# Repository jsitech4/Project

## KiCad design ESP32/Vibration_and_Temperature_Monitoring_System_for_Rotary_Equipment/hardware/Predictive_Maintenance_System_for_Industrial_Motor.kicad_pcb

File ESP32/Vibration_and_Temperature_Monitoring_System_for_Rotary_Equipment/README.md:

# Predictive Maintenance System for Industrial Motor

## Overview

This project is a complete **Predictive Maintenance System for Industrial Motor Monitoring** built around the **ESP32-S3 WROOM-1U** using a modular **PlatformIO** firmware structure.

The system is designed to monitor an industrial motor in real time, detect abnormal behaviour, estimate future fault risk, store large amounts of data for later analysis, and provide a local web dashboard for live viewing.

The system monitors:

- Motor vibration using an **ADXL345 accelerometer**
- Motor current using a **ZMCT103C current sensor**
- Motor temperature using a **DS18B20 temperature sensor**
- Motor operating state using a relay protection system

The system then calculates:

- Motor health score
- Motor risk score
- Fault level
- Worst operating metric
- Future fault estimate
- Maintenance recommendation

The project is designed so that the **SD card acts as the main backend and storage device**. If the SD card is not available, the firmware automatically uses the ESP32-S3 internal flash memory through **LittleFS** as fallback storage.

---

# Main Goal

The goal of this project is not only to display sensor values, but to behave like a real predictive maintenance prototype.

It should be able to:

1. Monitor motor operating condition
2. Log sensor and analysis data
3. Detect abnormal current, temperature, and vibration
4. Predict possible fault trends
5. Protect the motor using a relay
6. Notify the user using buzzer and LED indication
7. Display live status on LCD
8. Provide a web dashboard for future analysis
9. Store enough data for later engineering analysis

---

# Features

- ESP32-S3 WROOM-1U based controller
- ADXL345 vibration monitoring
- ZMCT103C current monitoring
- DS18B20 temperature monitoring
- 20x4 I2C LCD display
- Rotary encoder navigation
- Relay-based motor protection
- Active buzzer alarm
- Breathing onboard LED indicator
- SD card backend storage
- Internal LittleFS fallback storage
- CSV data logging
- Event logging
- Predictive maintenance analysis
- Motor health score calculation
- Risk score calculation
- Future fault estimation
- Local Wi-Fi Access Point
- Web dashboard for live monitoring
- Downloadable CSV logs from web dashboard
- Modular PlatformIO project structure
- Non-blocking firmware design

---

# Hardware Used

## Main Controller

- ESP32-S3 WROOM-1U

## Display

- 20x4 I2C LCD screen

## Sensors

- ADXL345 vibration sensor
- ZMCT103C current sensor
- DS18B20 temperature sensor

## Storage

- MicroSD card module
- ESP32-S3 internal flash memory using LittleFS as fallback

## User Input

- Rotary encoder with push button

## Output / Protection

- Relay module
- Active buzzer
- Onboard status LED

## Programming Interface

- CH340C USB-to-serial converter

---

# Pin Configuration

## I2C Bus

The LCD and ADXL345 share the same I2C bus.

| Function | ESP32-S3 GPIO |
|---|---|
| I2C SDA | GPIO8 |
| I2C SCL | GPIO9 |
| LCD SDA | GPIO8 |
| LCD SCL | GPIO9 |
| ADXL345 SDA | GPIO8 |
| ADXL345 SCL | GPIO9 |

---

## ADXL345 Vibration Sensor

| Function | ESP32-S3 GPIO |
|---|---|
| SDA | GPIO8 |
| SCL | GPIO9 |
| INT | GPIO10 |

---

## ZMCT103C Current Sensor

| Function | ESP32-S3 GPIO |
|---|---|
| Analog Output | GPIO1 |

> The ZMCT103C output must be conditioned properly and must not exceed the ESP32-S3 ADC input range.

---

## DS18B20 Temperature Sensor

| Function | ESP32-S3 GPIO |
|---|---|
| DATA | GPIO4 |

> Use a 4.7k pull-up resistor between DATA and 3.3V.

---

## SD Card Module

The SD card uses SPI mode.

| Function | ESP32-S3 GPIO |
|---|---|
| CS | GPIO5 |
| MOSI | GPIO11 |
| SCK | GPIO12 |
| MISO | GPIO13 |

---

## Rotary Encoder

| Function | ESP32-S3 GPIO |
|---|---|
| CLK | GPIO16 |
| DT | GPIO17 |
| SW | GPIO18 |

---

## Output Devices

| Function | ESP32-S3 GPIO |
|---|---|
| Buzzer | GPIO14 |
| Relay | GPIO21 |
| Status LED | GPIO48 |

---

## CH340C USB-to-Serial

| CH340C Pin | ESP32-S3 GPIO |
|---|---|
| TXD | GPIO44 RX0 |
| RXD | GPIO43 TX0 |
| GND | GND |

> TX and RX must be crossed.

---

## Boot and Reset Pins

| Function | Pin |
|---|---|
| BOOT | GPIO0 |
| EN / RESET | EN pin |

Recommended hardware:

- EN pulled up to 3.3V using 10k resistor
- EN connected to GND through 0.1uF capacitor
- BOOT button pulls GPIO0 to GND
- RESET button pulls EN to GND

---

# System Architecture

The firmware is arranged into independent modules.

```text
lib/
├── Actuators/
│   └── buzzer/
├── Communication/
│   └── local_server/
├── Control/
│   ├── error_handling/
│   ├── load_relay/
│   ├── maintenance_manager/
│   └── sleep_wake/
├── Display/
│   ├── lcd_screen/
│   └── led_indicator/
├── Input/
│   └── rotary_encoder/
├── Pins/
├── Sensors/
│   ├── current_sensor/
│   ├── temp_sensor/
│   └── vibration_sensor/
├── Storage/
│   └── sd_card/
├── System/
│   └── reset/
src/
└── main.cpp
```

---

# Firmware Flow

## Startup

On power-up, the firmware initializes:

1. Serial monitor
2. Pin configuration
3. Sensors
4. LCD
5. SD card
6. Internal LittleFS fallback storage
7. Relay protection module
8. Maintenance manager
9. Local web dashboard
10. LED and buzzer indication

---

## Main Loop

During operation, the loop updates all modules continuously:

1. Read current sensor
2. Read temperature sensor
3. Read vibration sensor
4. Calculate motor risk and health
5. Update relay protection logic
6. Update LCD display
7. Update local web dashboard
8. Log data to storage
9. Update buzzer and LED indicators

The design follows a non-blocking style as much as possible.

---

# Predictive Maintenance Logic

The predictive maintenance module uses live sensor values to estimate motor condition.

It monitors:

- temperature severity
- current severity
- vibration severity
- rate of change
- worst metric
- fault trend

The output of the analysis includes:

| Output | Description |
|---|---|
| Health Score | Estimated motor health in percent |
| Risk Score | Estimated fault risk in percent |
| Level | NORMAL, WARNING, CRITICAL, or FAULT |
| Worst Metric | The sensor value contributing most to the risk |
| Forecast | Estimated time before a fault condition |
| Recommendation | Maintenance advice based on condition |

---

# Fault Levels

## NORMAL

The motor is operating within acceptable range.

Typical behaviour:

- Relay remains ON
- Buzzer is OFF
- LED breathes normally
- Data continues logging

---

## WARNING

The motor is beginning to show abnormal behaviour.

Typical causes:

- rising vibration
- increasing temperature
- current approaching limit

Action:

- Continue monitoring
- Prepare maintenance inspection
- Check trend from dashboard logs

---

## CRITICAL

The motor is close to a fault limit.

Action:

- Schedule urgent inspection
- Check bearing, load, cooling, and supply condition
- Avoid prolonged operation

---

## FAULT

A fault threshold has been reached.

System response:

- Relay turns OFF
- Motor is disconnected
- Buzzer alarm starts
- LED changes behaviour
- Fault event is logged
- Dashboard shows fault condition

---

# Default Protection Thresholds

| Parameter | Threshold |
|---|---|
| Current | 5.0 A |
| Temperature | 70.0 °C |
| Vibration RMS | 2.5 g |

These values are firmware defaults and should be calibrated based on the actual motor rating and installation environment.

---

# Relay Protection Logic

The relay is used to protect the motor.

If any of the following conditions occur:

- current is above maximum limit
- temperature is above maximum limit
- vibration RMS is above maximum limit

Then:

- relay turns OFF
- buzzer alarm starts
- fault state is displayed
- event is stored in the log

The relay can also be controlled from the web dashboard, but the system will block unsafe relay ON operation while a fault is active.

---

# LCD Display

The 20x4 LCD displays real-time information.

LCD screens include:

## Screen 1: Live Motor Data

- Temperature
- Current
- Vibration RMS

## Screen 2: System Status

- Relay state
- Fault state
- SD card status
- Backend storage status

## Screen 3: Acceleration Data

- X axis
- Y axis
- Z axis

## Screen 4: Predictive Analysis

- Health score
- Risk score
- Worst metric
- Fault level

The rotary encoder is used to switch between screens.

---

# Web Dashboard

The ESP32-S3 creates a local Wi-Fi Access Point.

## Access Point

```text
SSID: MOTOR_PM_SYSTEM
Password: 12345678
```

## Dashboard Address

```text
http://192.168.4.1
```

The dashboard provides:

- live temperature
- live current
- live vibration
- acceleration values
- motor health score
- risk score
- condition level
- future fault estimate
- maintenance recommendation
- relay control
- fault clear button
- log now button
- CSV download buttons
- trend graph
- dark and light theme toggle

The dashboard is responsive and works on:

- phone
- tablet
- laptop
- desktop

---

# Web API Endpoints

## Root Dashboard

```text
/
```

Opens the main dashboard page.

---

## Live Status

```text
/api/status
```

Returns live sensor and analysis data as JSON.

Example fields:

```json
{
  "temperature_c": 35.50,
  "current_a": 1.250,
  "vibration_rms_g": 0.210,
  "risk_score": 18.5,
  "health_score": 81.5,
  "level": "NORMAL",
  "worst_metric": "Vibration",
  "forecast_text": "No rising fault trend detected",
  "relay_on": true,
  "fault": false,
  "backend": "SD CARD"
}
```

---

## Logs

```text
/api/logs
```

Returns recent motor, analysis, and event logs.

---

## Relay Control

```text
/api/relay?state=on
/api/relay?state=off
```

Controls the relay from the dashboard.

---

## Clear Fault

```text
/api/clear_fault
```

Clears the current latched fault condition.

---

## Log Immediately

```text
/api/log_now
```

Forces immediate log writing.

---

## Download CSV Logs

```text
/download/motor_log.csv
/download/analysis_log.csv
/download/event_log.csv
```

Downloads stored CSV files from the active backend.

---

# Storage Backend

The project uses two storage options.

## Primary Backend

```text
SD Card
```

The SD card is the main storage backend and is used for large data logging.

## Fallback Backend

```text
Internal LittleFS
```

If the SD card is missing or fails to initialize, the firmware automatically logs to internal flash memory.

This allows the system to continue operating even when the SD card is unavailable.

---

# Log Files

## Motor Log

```text
/motor_log.csv
```

Stores raw motor operating data.

Example:

```csv
millis,temp_c,current_a,vibration_rms_g,relay_on,fault
1000,32.40,1.220,0.120,1,0
6000,33.10,1.250,0.115,1,0
11000,34.00,1.300,0.140,1,0
```

---

## Analysis Log

```text
/analysis_log.csv
```

Stores predictive maintenance result.

Example:

```csv
millis,health_score,risk_score,level,worst_metric,forecast_minutes,recommendation
1000,91.5,8.5,NORMAL,Vibration,-1,Motor condition is normal
6000,78.0,22.0,NORMAL,Temperature,-1,Motor condition is normal
11000,54.0,46.0,WARNING,Vibration,180,Monitor closely
```

---

## Event Log

```text
/event_log.csv
```

Stores important system events.

Example:

```csv
millis,event,message
5000,BOOT,System started
24000,WARNING,Vibration trend increasing
45000,FAULT,Relay shutdown due to high temperature
```

---

# LED Behaviour

The onboard LED uses a PWM breathing effect.

## Normal Condition

- Breathing LED pattern
- Indicates firmware is running normally

## Fault Condition

- Fast blinking LED
- Indicates alarm or protection state

---

# Buzzer Behaviour

## Normal

- Buzzer OFF

## Fault

- Repeating alarm beep pattern

## Manual Feedback

The buzzer can also be used for short beep feedback in future menu actions.

---

# Sensor Calibration Notes

## ZMCT103C Current Sensor

The current value depends heavily on calibration.

The firmware uses a calibration factor to convert measured AC RMS voltage into current.

You should calibrate using:

1. A known load
2. A clamp meter
3. Serial monitor reading
4. Adjustment of calibration factor

Do not connect AC mains directly to the ESP32-S3.

---

## ADXL345 Vibration Sensor

The ADXL345 measures acceleration on X, Y, and Z axes.

The firmware calculates vibration RMS by comparing the measured acceleration magnitude against a base magnitude.

For better accuracy:

- mount the sensor firmly on the motor body
- avoid loose wires
- avoid placing it on flexible surfaces
- calibrate the baseline when the motor is in normal condition

---

## DS18B20 Temperature Sensor

For better temperature reading:

- attach the sensor to the motor body
- use thermal paste if possible
- keep the cable away from high-voltage switching lines
- use a 4.7k pull-up resistor

---

# Power and Safety Notes

- Use a stable 3.3V supply for the ESP32-S3
- Relay coils must not be driven directly from ESP32 GPIO
- Use a transistor, optocoupler, or relay module
- Use flyback protection for relay coils
- Keep AC and DC sections isolated
- Use common ground only where safe and required
- Add fuses and protection for industrial motor wiring
- Keep sensor signal wires away from motor power wires

---

# PlatformIO Configuration

Example environment:

```ini
[env:esp32-s3-devkitm-1]
platform = espressif32
board = esp32-s3-devkitm-1
framework = arduino
monitor_speed = 115200
```

Required libraries may include:

```ini
lib_deps =
  marcoschwartz/LiquidCrystal_I2C
  adafruit/Adafruit ADXL345
  adafruit/Adafruit Unified Sensor
  paulstoffregen/OneWire
  milesburton/DallasTemperature
```

Depending on your exact project structure, the library names may need small adjustment inside PlatformIO.

---

# Build and Upload

## Build

```bash
pio run
```

## Upload

```bash
pio run --target upload
```

## Serial Monitor

```bash
pio device monitor
```

or:

```bash
pio device monitor -b 115200
```

---

# Operating Guide

## Power On

1. Power the ESP32-S3 board
2. Wait for the LCD startup screen
3. Check that the status LED starts breathing
4. Confirm SD card status on LCD
5. Connect to the Wi-Fi AP if dashboard monitoring is needed

---

## View Dashboard

1. Open Wi-Fi settings on your phone or laptop
2. Connect to:

```text
MOTOR_PM_SYSTEM
```

3. Enter password:

```text
12345678
```

4. Open browser and go to:

```text
http://192.168.4.1
```

---

## Monitor Motor

The dashboard will show:

- temperature
- current
- vibration
- health score
- risk score
- fault forecast
- recommendation
- trend graph

---

## Download Logs

From the dashboard, use:

- Download Motor CSV
- Download Analysis CSV
- Download Events CSV

These files can be opened in:

- Excel
- Google Sheets
- Python
- MATLAB
- Power BI

---

# Data Analysis Use

The logged CSV data can be used for:

- trend analysis
- fault history review
- machine learning dataset creation
- motor condition classification
- vibration behaviour analysis
- current overload study
- maintenance scheduling

---

# Future Improvements

- Machine learning model for motor fault classification
- Web-based threshold calibration
- MQTT support
- Cloud sync
- OTA firmware updates
- Email or SMS fault notification
- More vibration features such as peak, crest factor, and FFT
- Motor runtime counter
- Bearing fault frequency analysis
- Multi-motor monitoring
- User login for dashboard
- Historical charts from stored CSV
- Automatic report generation

---

# Troubleshooting

## LCD Not Showing Text

Check:

- LCD I2C address
- SDA and SCL wiring
- 5V or 3.3V compatibility
- I2C pull-up resistors

Common LCD addresses:

```text
0x27
0x3F
```

---

## SD Card Not Detected

Check:

- SD CS pin
- SPI wiring
- SD card formatting
- 3.3V compatibility
- card inserted properly

If SD card is missing, the system should fall back to internal LittleFS storage.

---

## Current Reading Is Wrong

Check:

- ZMCT103C calibration factor
- ADC input voltage range
- burden resistor and conditioning circuit
- real load current using clamp meter

---

## Vibration Reading Is Too High

Check:

- sensor mounting
- loose wires
- motor frame vibration
- ADXL345 orientation
- baseline calibration

---

## Dashboard Not Opening

Check:

- phone is connected to `MOTOR_PM_SYSTEM`
- open `http://192.168.4.1`
- ensure local server module is started in `main.cpp`
- check serial monitor for AP IP address

---

# Author

Egbe Raymond

Electrical / Electronic Engineer  
Embedded Systems Developer  
Full Stack Developer

---

# License

This project is intended for educational, industrial prototype, and development purposes.

Use proper electrical safety practices when testing with industrial motors and mains-powered equipment.

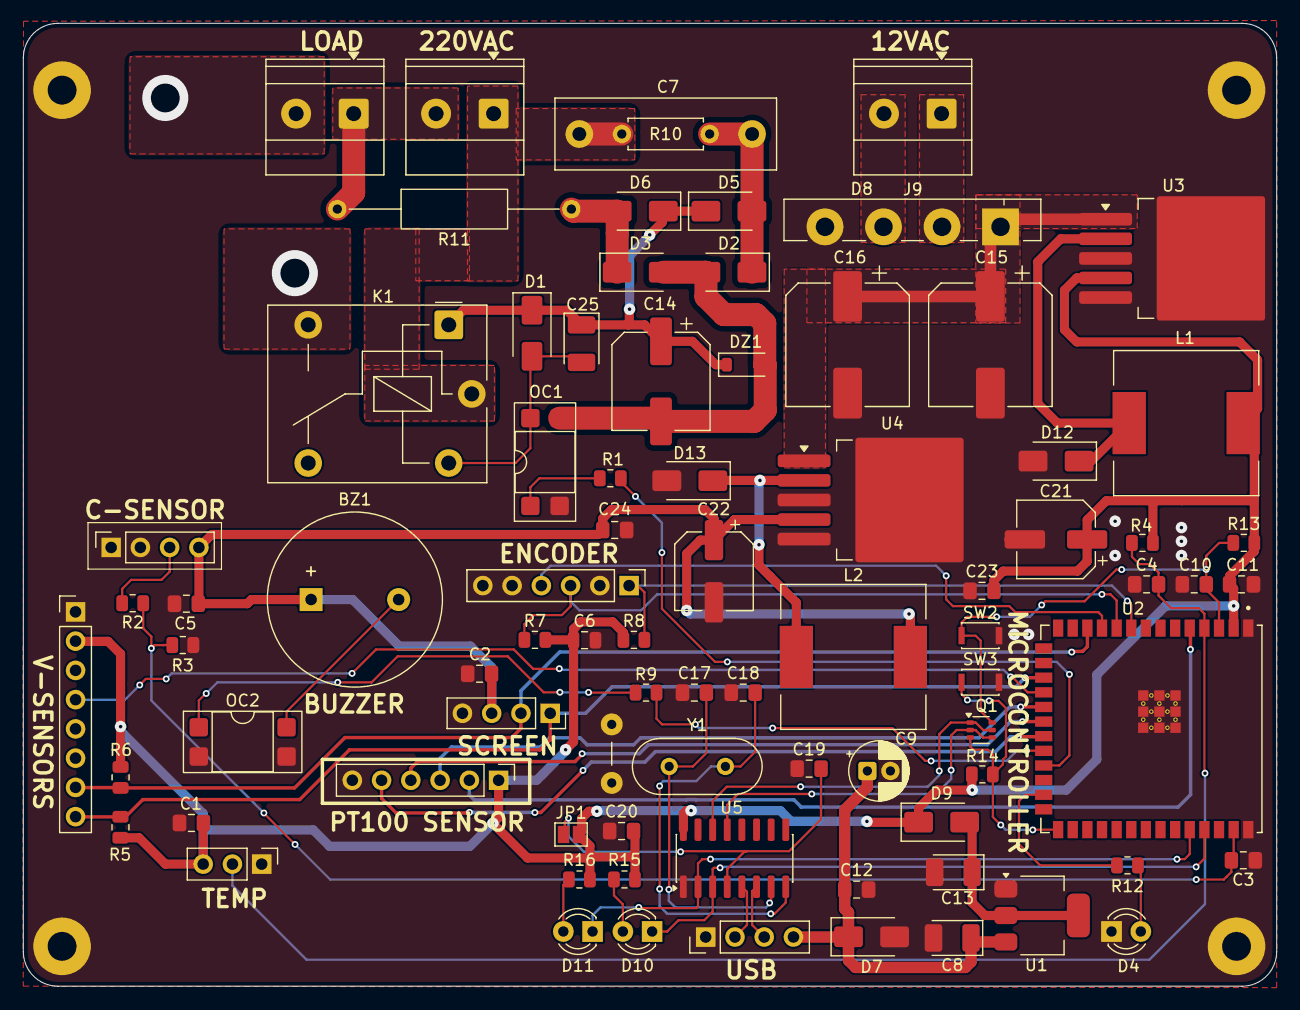
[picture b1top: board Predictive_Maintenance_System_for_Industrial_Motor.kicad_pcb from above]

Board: 2 copper layers, 108.8 x 83.6 mm, 81 parts (0 on the bottom side), 51 nets.

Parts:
BZ1: Buzzer; Buzzer_15x7.5RM7.6
C1, C2, C3, C4, C5, C11, C12, C19, C20, C23, C24: 100nF; C_0805_2012Metric_Pad1.18x1.45mm_HandSolder
C6: 104; C_0805_2012Metric
C7: 145J400V; C_Rect_L19.0mm_W6.0mm_P15.00mm_MKS4
C8, C13, C25: 4.7uF/16V; CP_EIA-3528-21_Kemet-B_HandSolder
C9: 10uF_16V; CP_Radial_D5.0mm_P2.00mm
C10: 470nF; C_0805_2012Metric_Pad1.18x1.45mm_HandSolder
C14: 470uF/25V; CP_Elec_8x11.9
C15, C16: 680uF_35V; CP_Elec_10x12.5
C17, C18: 22pF; C_0805_2012Metric_Pad1.18x1.45mm_HandSolder
C21, C22: 220uF_16V; CP_Elec_6.3x7.7
D1: 1N4007; D_SMA
D2, D3, D5, D6: SM4001; D_SMA
D4, D10: Red; LED_D3.0mm
D7, D9: 1N5819; D_SMA
D8: GBU8M; Diode_Bridge_Vishay_GBU
D11: Green; LED_D3.0mm
D12, D13: 1N5824; D_SMA
DZ1: CMZ12; D_SOD-123
J1: DS18B20; PinHeader_1x03_P2.54mm_Vertical
J2: CURRENT SENSOR; PinSocket_1x04_P2.54mm_Vertical
J3: OLED SCREEN; PinSocket_1x04_P2.54mm_Vertical
J4: LOAD; TerminalBlock_Phoenix_MKDS-1,5-2_1x02_P5.00mm_Horizontal
J5: 220VAC; TerminalBlock_Phoenix_MKDS-1,5-2_1x02_P5.00mm_Horizontal
J6: MPU6050; PinHeader_1x08_P2.54mm_Vertical
J7: SD MODULE; PinHeader_1x06_P2.54mm_Vertical
J8: USB_C Conn; PinHeader_1x04_P2.54mm_Vertical
J9: 12VAC; TerminalBlock_Phoenix_MKDS-1,5-2_1x02_P5.00mm_Horizontal
JP1: SolderJumper-2_P1.3mm_Open_Pad1.0x1.5mm
K1: FINDER-36.11; Relay_SPDT_Finder_36.11
L1, L2: 33uH; L_12x12mm_H6mm
OC1, OC2: PC817XI; DIP-4_W7.62mm_SMDSocket_SmallPads
Q1: UMH3N; SOT-363_SC-70-6
R1, R4, R5, R6, R7, R8, R9, R13, R14: 10k; R_0805_2012Metric
R2: 1k; R_0805_2012Metric
R3: 2k; R_0805_2012Metric
R10: 1M; R_Axial_DIN0207_L6.3mm_D2.5mm_P7.62mm_Horizontal
R11: 330R/2W; R_Axial_DIN0309_L9.0mm_D3.2mm_P20.32mm_Horizontal
R12, R15, R16: 330R; R_0805_2012Metric
SW1: RotaryEncoder; PinHeader_1x06_P2.54mm_Vertical
SW2: RESET; SW_SPST_CK_KXT3
SW3: FLASH; SW_SPST_CK_KXT3
U1: AMS1117-3.3; SOT-223-3_TabPin2
U2: ESP32-S3-WROOM-1U-N16R8
U3: LM2596S-3.3V; TO-263-5_TabPin6
U4: LM2596S-5V; TO-263-5_TabPin6
U5: CH340C; SOIC-16_3.9x9.9mm_P1.27mm
Y1: 12MHz; Crystal_HC49-4H_Vertical

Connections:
+3.3V: C1.2, C6.1, C11.2, C20.1, C21.1, C23.2, D9.1 (K), J1.3, J6.2, J7.1, JP1.2 (B), L1.2, R4.1, R5.1, R6.1, R7.2, R8.1, R13.2, R14.2, R15.1, R16.1, U2.2 (3V3), U3.4 (FB), U5.16 (VCC)
+5V: BZ1.1 (+), C2.1, C5.2, C22.1, C24.2, J2.4, J3.3, L2.2, U4.4 (FB)
/+: J8.2, U5.5 (UD+)
/-: J8.3, U5.6 (UD-)
/CS: J7.2, U2.5 (IO5)
/DTR: Q1.2 (B1), Q1.4 (E2), U5.13 (~DTR)
/EN: C10.2, Q1.6 (C1), R13.1, SW2.2, U2.3 (EN)
/GPIO0: Q1.3 (C2), R14.1, SW3.2, U2.27 (IO0)
/GPIO1: C3.2, R2.2, R3.1, U2.39 (IO1)
/GPIO4: C4.2, J1.2, R4.2, U2.4 (IO4)
/GPIO14: R9.1, U2.22 (IO14)
/GPIO16: R8.2, SW1.1 (A), U2.9 (IO16)
/GPIO17: R7.1, SW1.3 (B), U2.10 (IO17)
/GPIO18: SW1.4 (S1), U2.11 (IO18)
/GPIO21: R1.1, U2.23 (IO21)
/GPIO43/TX: D10.1 (K), U2.37 (TXD0), U5.3 (RXD)
/GPIO44/RX: D11.1 (K), U2.36 (RXD0), U5.2 (TXD)
/GPIO48: R12.1, U2.25 (IO48)
/INT1: J6.4, U2.18 (IO10)
/LIVE: C7.2, J5.1, K1.11, R10.2
/MISO: J7.5, U2.21 (IO13)
/MOSI: J7.3, U2.19 (IO11)
/NEUTRAL: J4.1, J5.2, R11.1
/RTS: Q1.1 (E1), Q1.5 (B2), U5.14 (~RTS)
/SCK: J7.4, U2.20 (IO12)
/SCL: J3.1, J6.8, R5.2, U2.17 (IO9)
/SDA: J3.2, J6.7, R6.2, U2.12 (IO8)
/VCC1: C15.1, C16.1, D8.1 (+), U3.1 (VIN), U4.1 (VIN)
GND: C1.1, C2.2, C3.1, C4.1, C5.1, C6.2, C8.2, C9.2, C10.1, C11.1, C12.1, C13.2, C15.2, C16.2, C17.2, C18.2, C19.1, C20.2, C21.2, C22.2, C23.1, C24.1, D4.1 (K), D7.2 (A), D8.4 (-), D12.2 (A), D13.2 (A), J1.1, J2.1, J2.2, J3.4, J6.1, J7.6, J8.1, OC1.2, OC2.2, OC2.3, R3.2, SW1.2 (C), SW1.5 (S2), SW1.6 (MP), SW2.1, SW3.1, U1.1 (GND), U2.1 (GND), U2.40 (GND), U2.41 (GND), U3.3 (GND), U3.5 (~ON/OFF), U3.6 (GND), U4.3 (GND), U4.5 (~ON/OFF), U4.6 (GND), U5.1 (GND)
GNDA: C14.2, D2.2 (A), D3.2 (A), DZ1.2 (A), OC1.3
unnamed: BZ1.2 (-), OC2.4
unnamed: C25.2, D1.2 (A), K1.A2, OC1.4
unnamed: C7.1, D2.1 (K), D5.2 (A), R10.1
unnamed: D3.1 (K), D6.2 (A), R11.2
unnamed: D4.2 (A), R12.2
unnamed: C8.1, C9.1, C12.2, D7.1 (K), J8.4, U1.3 (VI)
unnamed: C13.1, D9.2 (A), U1.2 (VO)
unnamed: D10.2 (A), R15.2
unnamed: D11.2 (A), R16.2
unnamed: D12.1 (K), L1.1, U3.2 (OUT)
unnamed: D13.1 (K), L2.1, U4.2 (OUT)
unnamed: J2.3, R2.1
unnamed: J4.2, K1.14
unnamed: D8.2, J9.1
unnamed: D8.3, J9.2
unnamed: C19.2, JP1.1 (A), U5.4 (V3)
unnamed: OC1.1, R1.2
unnamed: OC2.1, R9.2
unnamed: C17.1, U5.7 (Xi), Y1.2
unnamed: C18.1, U5.8 (Xo), Y1.1
VCC2: C14.1, C25.1, D1.1 (K), D5.1 (K), D6.1 (K), DZ1.1 (K), K1.A1

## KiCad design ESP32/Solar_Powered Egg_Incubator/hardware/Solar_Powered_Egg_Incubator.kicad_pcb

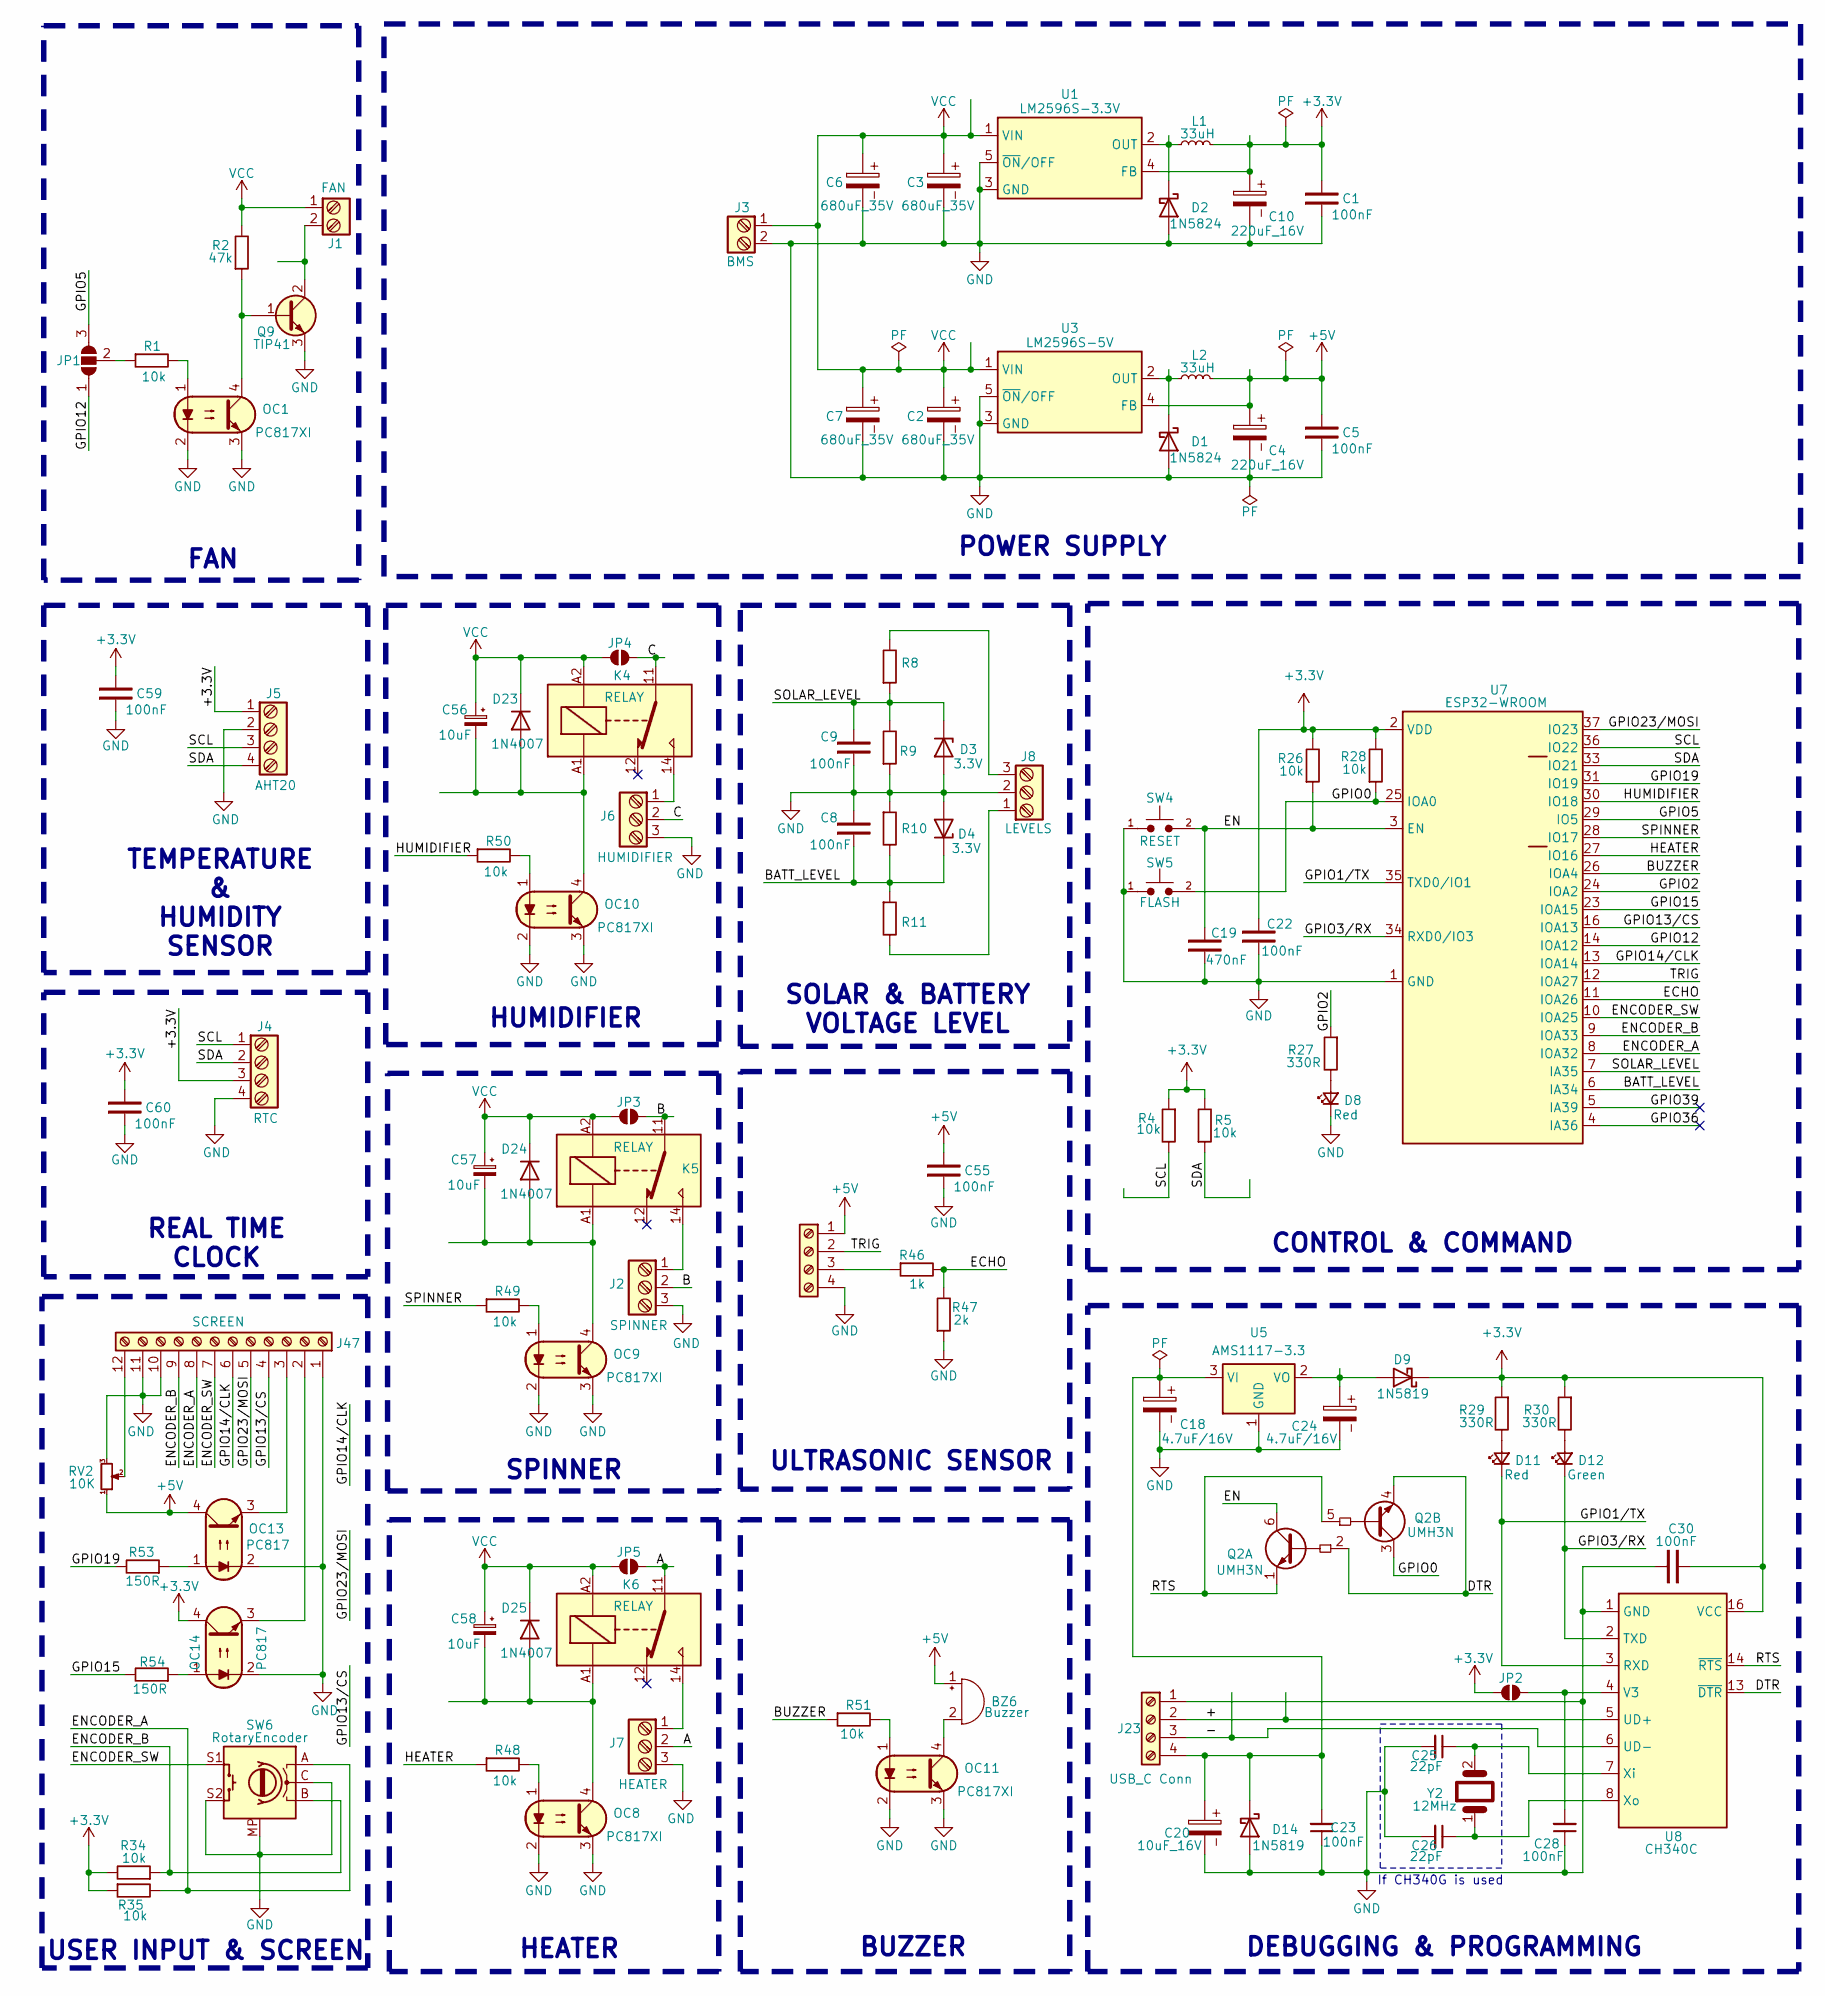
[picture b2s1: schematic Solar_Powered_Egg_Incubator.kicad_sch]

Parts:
BZ6: Buzzer; Buzzer_15x7.5RM7.6
C1, C5, C8, C9, C22, C23, C28, C30, C55, C59, C60: 100nF; C_0805_2012Metric_Pad1.18x1.45mm_HandSolder
C2, C3, C6, C7: 680uF_35V; CP_Elec_10x12.5
C4, C10: 220uF_16V; CP_Elec_6.3x7.7
C18, C24: 4.7uF/16V; CP_EIA-3528-21_Kemet-B_HandSolder
C19: 470nF; C_0805_2012Metric_Pad1.18x1.45mm_HandSolder
C20: 10uF_16V; CP_Radial_D5.0mm_P2.00mm
C25, C26: 22pF; C_0805_2012Metric_Pad1.18x1.45mm_HandSolder
C56, C57, C58: 10uF; CP_EIA-3528-21_Kemet-B_HandSolder
D1, D2: 1N5824; D_SMA
D3, D4: 3.3V; D_SOD-123
D8, D11: Red; LED_D3.0mm
D9, D14: 1N5819; D_SMA
D12: Green; LED_D3.0mm
D23, D24, D25: 1N4007; D_SMA
J1: FAN; TerminalBlock_Phoenix_PT-1,5-2-5.0-H_1x02_P5.00mm_Horizontal
J2: SPINNER; TerminalBlock_Phoenix_MKDS-1,5-3_1x03_P5.00mm_Horizontal
J3: BMS; TerminalBlock_Phoenix_PT-1,5-2-5.0-H_1x02_P5.00mm_Horizontal
J4: RTC; PinHeader_1x04_P2.54mm_Vertical
J5: AHT20; PinHeader_1x04_P2.54mm_Vertical
J6: HUMIDIFIER; TerminalBlock_Phoenix_MKDS-1,5-3_1x03_P5.00mm_Horizontal
J7: HEATER; TerminalBlock_Phoenix_MKDS-1,5-3_1x03_P5.00mm_Horizontal
J8: LEVELS; PinHeader_1x03_P2.54mm_Vertical
J23: USB_C Conn; PinHeader_1x04_P2.54mm_Vertical
J42: Ultra Sonic; PinSocket_1x04_P2.54mm_Vertical
J47: SCREEN; PinHeader_1x12_P2.54mm_Vertical
JP1: SolderJumper_3_Open; SolderJumper-3_P1.3mm_Open_Pad1.0x1.5mm
JP2, JP3, JP4, JP5: SolderJumper-2_P1.3mm_Open_Pad1.0x1.5mm
K4, K5, K6: RELAY; Relay_SPDT_Finder_36.11
L1, L2: 33uH; L_12x12mm_H6mm
OC1, OC8, OC9, OC10, OC11: PC817XI; SMDIP-4_W9.53mm
OC13, OC14: PC817; SMDIP-4_W9.53mm
Q2: UMH3N; SOT-363_SC-70-6
Q9: TIP41; TO-220-3_Vertical
R1, R4, R5, R26, R28, R34, R35, R48, R49, R50, R51: 10k; R_0805_2012Metric
R2: 47k; R_0805_2012Metric
R8, R9, R10, R11: NS; R_0805_2012Metric
R27, R29, R30: 330R; R_0805_2012Metric
R46: 1k; R_0805_2012Metric
R47: 2k; R_0805_2012Metric
R53, R54: 150R; R_0805_2012Metric
RV2: 10K; Potentiometer_Bourns_3296W_Vertical
SW4: RESET; SW_SPST_CK_KXT3
SW5: FLASH; SW_SPST_CK_KXT3
SW6: RotaryEncoder; PinHeader_1x06_P2.54mm_Vertical
U1: LM2596S-3.3V; TO-263-5_TabPin6
U3: LM2596S-5V; TO-263-5_TabPin6
U5: AMS1117-3.3; SOT-223-3_TabPin2
U7: ESP32-WROOM; ESP32-WROOM-32
U8: CH340C; SOIC-16_3.9x9.9mm_P1.27mm
Y2: 12MHz; Crystal_HC49-4H_Vertical

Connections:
+3.3V: C1.2, C10.1, C22.2, C30.1, C59.2, C60.2, D9.1 (K), J4.3, J5.1, JP2.2 (B), L1.2, OC14.4, R4.1, R5.2, R26.2, R28.2, R29.1, R30.1, R34.2, R35.1, U1.4 (FB), U7.2 (VDD), U8.16 (VCC)
+5V: BZ6.1 (+), C4.1, C5.2, C55.2, J42.1, L2.2, OC13.4, RV2.1, U3.4 (FB)
/+: J23.2, U8.5 (UD+)
/-: J23.3, U8.6 (UD-)
/A: J7.2, JP5.1 (A), K6.11
/B: J2.2, JP3.1 (A), K5.11
/BATT_LEVEL: C8.1, D4.1 (K), R10.2, R11.1, U7.6 (IA34)
/BUZZER: R51.1, U7.26 (IOA4)
/C: J6.2, JP4.1 (A), K4.11
/DTR: Q2.2 (B1), Q2.4 (E2), U8.13 (~DTR)
/ECHO: R46.2, R47.2, U7.11 (IOA26)
/EN: C19.2, Q2.6 (C1), R26.1, SW4.2, U7.3 (EN)
/ENCODER_A: J47.8, R35.2, SW6.A, U7.8 (IOA32)
/ENCODER_B: J47.9, R34.1, SW6.B, U7.9 (IOA33)
/ENCODER_SW: J47.7, SW6.S1, U7.10 (IOA25)
/GPIO0: Q2.3 (C2), R28.1, SW5.2, U7.25 (IOA0)
/GPIO1/TX: D11.1 (K), U7.35 (TXD0/IO1), U8.3 (RXD)
/GPIO2: R27.1, U7.24 (IOA2)
/GPIO3/RX: D12.1 (K), U7.34 (RXD0/IO3), U8.2 (TXD)
/GPIO5: JP1.3 (B), U7.29 (IO5)
/GPIO12: JP1.1 (A), U7.14 (IOA12)
/GPIO13/CS: J47.4, U7.16 (IOA13)
/GPIO14/CLK: J47.6, U7.13 (IOA14)
/GPIO15: R54.2, U7.23 (IOA15)
/GPIO19: R53.2, U7.31 (IO19)
/GPIO23/MOSI: J47.5, U7.37 (IO23)
/GPIO36: U7.4 (IA36)
/GPIO39: U7.5 (IA39)
/HEATER: R48.1, U7.27 (IO16)
/HUMIDIFIER: R50.1, U7.30 (IO18)
/RTS: Q2.1 (E1), Q2.5 (B2), U8.14 (~RTS)
/SCL: J4.1, J5.3, R4.2, U7.36 (IO22)
/SDA: J4.2, J5.4, R5.1, U7.33 (IO21)
/SOLAR_LEVEL: C9.2, D3.1 (K), R8.1, R9.2, U7.7 (IA35)
/SPINNER: R49.1, U7.28 (IO17)
/TRIG: J42.2, U7.12 (IOA27)
GND: C1.1, C2.2, C3.2, C4.2, C5.1, C6.2, C7.2, C8.2, C9.1, C10.2, C18.2, C19.1, C20.2, C22.1, C23.1, C24.2, C25.2, C26.2, C28.1, C30.2, C55.1, C59.1, C60.1, D1.2 (A), D2.2 (A), D3.2 (A), D4.2 (A), D8.1 (K), D14.2 (A), J2.3, J3.2, J4.4, J5.2, J6.3, J7.3, J8.2, J23.1, J42.4, J47.1, J47.10, J47.11, OC1.2, OC1.3, OC8.2, OC8.3, OC9.2, OC9.3, OC10.2, OC10.3, OC11.2, OC11.3, OC13.2, OC14.2, Q9.3 (E), R9.1, R10.1, R47.1, RV2.3, SW4.1, SW5.1, SW6.C, SW6.MP, SW6.S2, U1.3 (GND), U1.5 (~ON/OFF), U1.6 (GND), U3.3 (GND), U3.5 (~ON/OFF), U3.6 (GND), U5.1 (GND), U7.1 (GND), U7.15 (GND), U7.38 (GND), U7.39 (GND), U8.1 (GND)
unnamed: BZ6.2 (-), OC11.4
unnamed: D1.1 (K), L2.1, U3.2 (OUT)
unnamed: D2.1 (K), L1.1, U1.2 (OUT)
unnamed: D8.2 (A), R27.2
unnamed: C24.1, D9.2 (A), U5.2 (VO)
unnamed: D11.2 (A), R29.2
unnamed: D12.2 (A), R30.2
unnamed: C18.1, C20.1, C23.2, D14.1 (K), J23.4, U5.3 (VI)
unnamed: C56.2, D23.2 (A), K4.A1, OC10.4
unnamed: C57.2, D24.2 (A), K5.A1, OC9.4
unnamed: C58.2, D25.2 (A), K6.A1, OC8.4
unnamed: J2.1, K5.14
unnamed: J6.1, K4.14
unnamed: J7.1, K6.14
unnamed: J8.1, R11.2
unnamed: J8.3, R8.2
unnamed: J42.3, R46.1
unnamed: J47.2, OC14.3
unnamed: J47.3, OC13.3
unnamed: J47.12, RV2.2
unnamed: JP1.2 (C), R1.1
unnamed: C28.2, JP2.1 (A), U8.4 (V3)
unnamed: OC1.1, R1.2
unnamed: OC8.1, R48.2
unnamed: OC9.1, R49.2
unnamed: OC10.1, R50.2
unnamed: OC11.1, R51.2
unnamed: OC13.1, R53.1
unnamed: OC14.1, R54.1
unnamed: OC1.4, Q9.1 (B), R2.1
unnamed: J1.2, Q9.2 (C)
unnamed: C25.1, U8.7 (Xi), Y2.2
unnamed: C26.1, U8.8 (Xo), Y2.1
VCC: C2.1, C3.1, C6.1, C7.1, C56.1, C57.1, C58.1, D23.1 (K), D24.1 (K), D25.1 (K), J1.1, J3.1, JP3.2 (B), JP4.2 (B), JP5.2 (B), K4.A2, K5.A2, K6.A2, R2.2, U1.1 (VIN), U3.1 (VIN)

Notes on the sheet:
HUMIDIFIER
DEBUGGING & PROGRAMMING
CONTROL & COMMAND
ULTRASONIC SENSOR
REAL TIME CLOCK
SPINNER
HEATER
If CH340G is used
POWER SUPPLY
BUZZER
TEMPERATURE & HUMIDITY SENSOR
USER INPUT & SCREEN
FAN
SOLAR & BATTERY VOLTAGE LEVEL

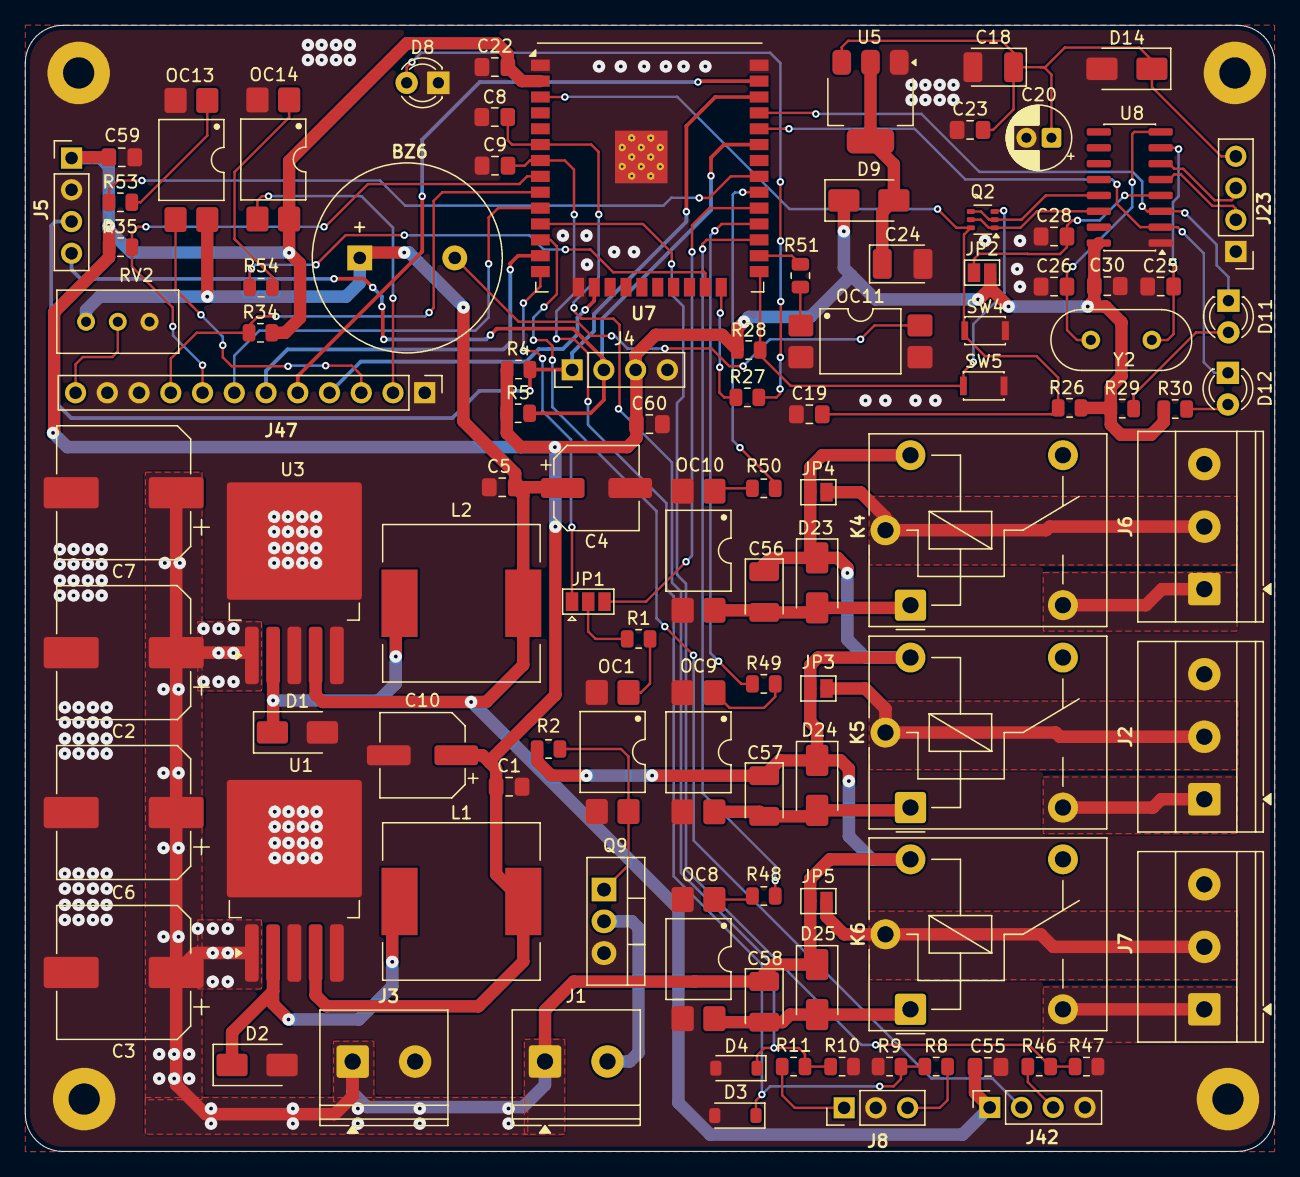
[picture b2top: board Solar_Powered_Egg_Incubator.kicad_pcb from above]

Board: 2 copper layers, 100.0 x 90.1 mm, 101 parts (0 on the bottom side), 69 nets.

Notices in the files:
ESP32/Vibration_and_Temperature_Monitoring_System_for_Rotary_Equipment/README.md:
License:
This project is intended for educational, industrial prototype, and development purposes.
Use proper electrical safety practices when testing with industrial motors and mains-powered equipment.
